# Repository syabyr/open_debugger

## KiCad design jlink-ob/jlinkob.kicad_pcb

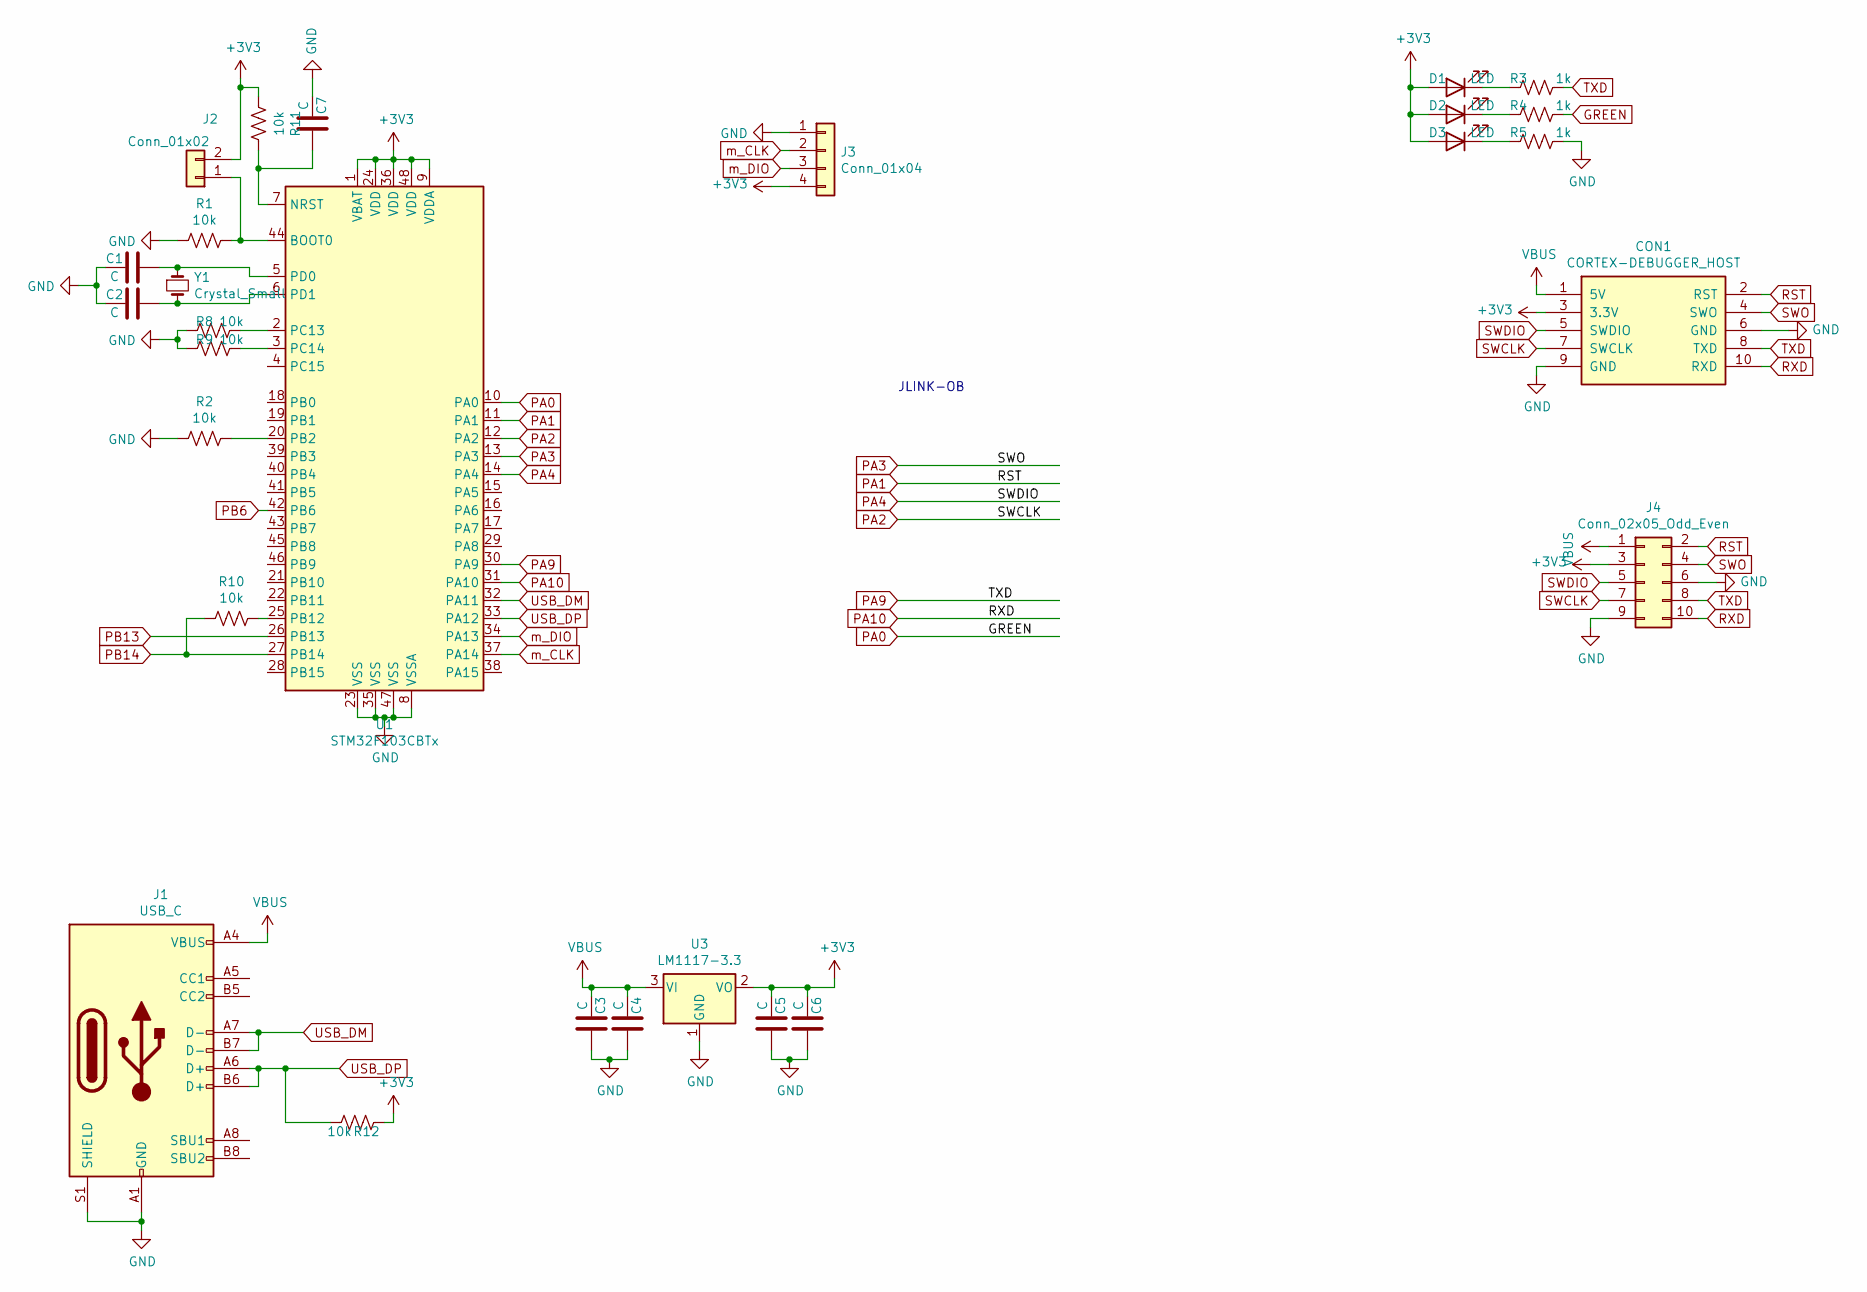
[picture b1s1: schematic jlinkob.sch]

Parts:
C1, C2, C3, C5, C7: C; C_0603_1608Metric
C4, C6: C; CP_EIA-7343-43_Kemet-X_Pad2.25x2.55mm_HandSolder
CON1: CORTEX-DEBUGGER_HOST; debugger_2x05_P1.27mm_Vertical
D1, D2, D3: LED; LED_0603_1608Metric
J1: USB_C
J2: Conn_01x02; PinHeader_1x02_P2.00mm_Vertical
J3: Conn_01x04; PinHeader_1x04_P2.00mm_Vertical
J4: Conn_02x05_Odd_Even; S_2.54_2_5P_JX
R1, R2, R8, R9, R10, R11, R12: 10k; R_0603_1608Metric
R3, R4, R5: 1k; R_0603_1608Metric
U1: STM32F103CBTx; LQFP-48_7x7mm_P0.5mm
U3: LM1117-3.3; SOT-223
Y1: Crystal_Small; Crystal_SMD_5032-2Pin_5.0x3.2mm

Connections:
+3V3: C5.2, C6.2, CON1.3 (3.3V), D1.2 (A), D2.2 (A), D3.2 (A), J2.2, J3.4, J4.3, R11.2, R12.2, U1.1 (VBAT), U1.9 (VDDA), U1.24 (VDD), U1.36 (VDD), U1.48 (VDD), U3.2 (VO)
GND: C1.2, C2.2, C3.1, C4.1, C5.1, C6.1, C7.2, CON1.6 (GND), CON1.9 (GND), J1.A1 (GND), J1.A12 (GND), J1.B1 (GND), J1.B12 (GND), J1.S1 (SHIELD), J3.1, J4.6, J4.9, R1.2, R2.2, R5.1, R8.2, R9.2, U1.8 (VSSA), U1.23 (VSS), U1.35 (VSS), U1.47 (VSS), U3.1 (GND)
GREEN: R4.1, U1.10 (PA0)
unnamed: C1.1, U1.5 (PD0), Y1.1
unnamed: C2.1, U1.6 (PD1), Y1.2
unnamed: C7.1, R11.1, U1.7 (NRST)
unnamed: D1.1 (K), R3.2
unnamed: D2.1 (K), R4.2
unnamed: D3.1 (K), R5.2
unnamed: J2.1, R1.1, U1.44 (BOOT0)
unnamed: R2.1, U1.20 (PB2)
unnamed: R8.1, U1.2 (PC13)
unnamed: R9.1, U1.3 (PC14)
unnamed: R10.1, U1.25 (PB12)
PA1: CON1.2 (RST), J4.2, U1.11 (PA1)
PA2: CON1.7 (SWCLK), J4.7, U1.12 (PA2)
PA3: CON1.4 (SWO), J4.4, U1.13 (PA3)
PA4: CON1.5 (SWDIO), J4.5, U1.14 (PA4)
PA9: CON1.8 (TXD), J4.8, R3.1, U1.30 (PA9)
PA10: CON1.10 (RXD), J4.10, U1.31 (PA10)
PB6: U1.42 (PB6)
PB13: U1.26 (PB13)
PB14: R10.2, U1.27 (PB14)
USB_DM: J1.A7 (D-), J1.B7 (D-), U1.32 (PA11)
USB_DP: J1.A6 (D+), J1.B6 (D+), R12.1, U1.33 (PA12)
VBUS: C3.2, C4.2, CON1.1 (5V), J1.A4 (VBUS), J1.A9 (VBUS), J1.B4 (VBUS), J1.B9 (VBUS), J4.1, U3.3 (VI)
m_CLK: J3.2, U1.37 (PA14)
m_DIO: J3.3, U1.34 (PA13)

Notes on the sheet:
JLINK-OB

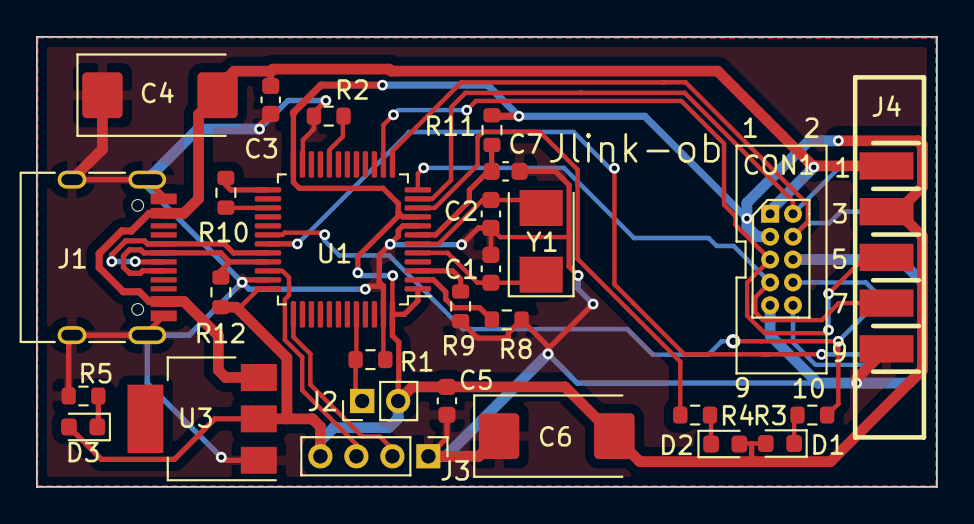
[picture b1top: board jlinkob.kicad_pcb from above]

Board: 2 copper layers, 50.0 x 25.0 mm, 28 parts (0 on the bottom side), 26 nets.

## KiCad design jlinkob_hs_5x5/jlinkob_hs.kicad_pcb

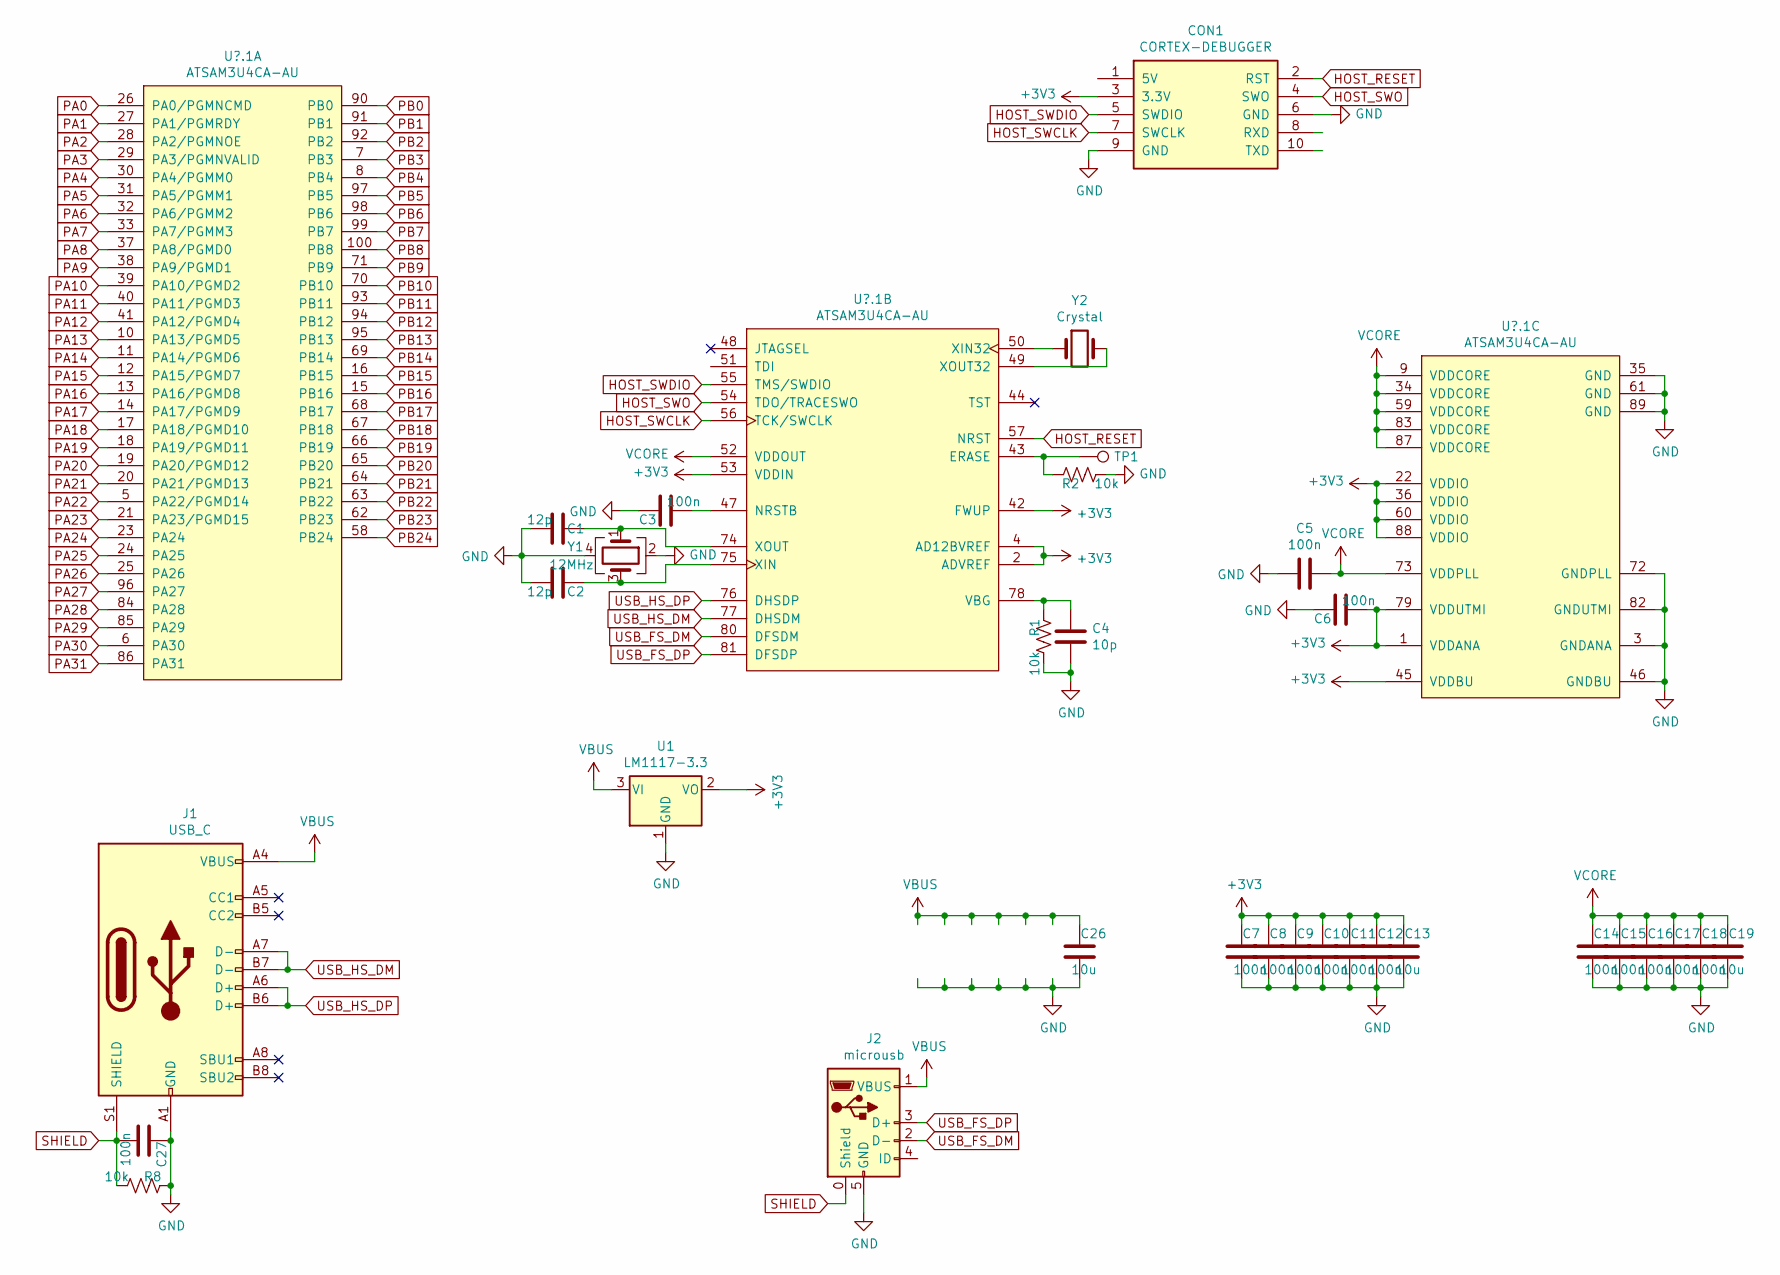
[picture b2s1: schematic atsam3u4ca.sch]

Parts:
C1, C2: 12p; C_0402_1005Metric_Pad0.74x0.62mm_HandSolder
C3, C5, C6, C7, C8, C9, C10, C11, C12, C14, C15, C16, C17, C18, C27: 100n; C_0402_1005Metric_Pad0.74x0.62mm_HandSolder
C4: 10p; C_0402_1005Metric_Pad0.74x0.62mm_HandSolder
C13, C26: 10u; C_1206_3216Metric_Pad1.33x1.80mm_HandSolder
C19: 10u; C_0402_1005Metric_Pad0.74x0.62mm_HandSolder
CON1: CORTEX-DEBUGGER; debugger_2x05_P1.27mm_Vertical
J1: USB_C
J2: microusb; USB_Micro-B_Wuerth_629105150521_CircularHoles
R1, R2, R8: 10k; R_0402_1005Metric_Pad0.72x0.64mm_HandSolder
TP1: TestPoint; TestPoint_0.5
U1: LM1117-3.3; SOT-223-3_TabPin2
U?.1: ATSAM3U4CA-AU; QFP50P1600X1600X160-100N
Y1: 12MHz; Crystal_SMD_3225-4Pin_3.2x2.5mm
Y2: Crystal; Crystal_SMD_MicroCrystal_CC7V-T1A-2Pin_3.2x1.5mm_HandSolder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

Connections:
+3V3: C6.2, C7.1, C8.1, C9.1, C10.1, C11.1, C12.1, C13.1, CON1.3 (3.3V), U1.2 (VO), U?.1.1 (VDDANA), U?.1.2 (ADVREF), U?.1.4 (AD12BVREF), U?.1.22 (VDDIO), U?.1.36 (VDDIO), U?.1.42 (FWUP), U?.1.45 (VDDBU), U?.1.53 (VDDIN), U?.1.60 (VDDIO), U?.1.79 (VDDUTMI), U?.1.88 (VDDIO); also elsewhere on the board
GND: C1.1, C2.1, C3.1, C4.2, C5.1, C6.1, C7.2, C8.2, C9.2, C10.2, C11.2, C12.2, C13.2, C14.2, C15.2, C16.2, C17.2, C18.2, C19.2, C26.2, C27.1, CON1.6 (GND), CON1.9 (GND), J1.A1 (GND), J1.A12 (GND), J1.B1 (GND), J1.B12 (GND), J2.5 (GND), R1.2, R2.2, R8.1, U1.1 (GND), U?.1.3 (GNDANA), U?.1.35 (GND), U?.1.46 (GNDBU), U?.1.61 (GND), U?.1.72 (GNDPLL), U?.1.82 (GNDUTMI), U?.1.89 (GND), Y1.2, Y1.4; also elsewhere on the board
HOST_RESET: CON1.2 (RST), U?.1.57 (NRST); also elsewhere on the board
HOST_SWCLK: CON1.7 (SWCLK), U?.1.56 (TCK/SWCLK)
HOST_SWDIO: CON1.5 (SWDIO), U?.1.55 (TMS/SWDIO)
HOST_SWO: CON1.4 (SWO), U?.1.54 (TDO/TRACESWO)
unnamed: C1.2, U?.1.74 (XOUT), Y1.1
unnamed: C2.2, U?.1.75 (XIN), Y1.3
unnamed: C3.2, U?.1.47 (NRSTB)
unnamed: C4.1, R1.1, U?.1.78 (VBG)
unnamed: R2.1, TP1.1, U?.1.43 (ERASE)
unnamed: U?.1.49 (XOUT32), Y2.2
unnamed: U?.1.50 (XIN32), Y2.1
PA0: U?.1.26 (PA0/PGMNCMD); also elsewhere on the board
PA1: U?.1.27 (PA1/PGMRDY); also elsewhere on the board
PA2: U?.1.28 (PA2/PGMNOE); also elsewhere on the board
PA3: U?.1.29 (PA3/PGMNVALID); also elsewhere on the board
PA4: U?.1.30 (PA4/PGMM0); also elsewhere on the board
PA5: U?.1.31 (PA5/PGMM1); also elsewhere on the board
PA6: U?.1.32 (PA6/PGMM2); also elsewhere on the board
PA7: U?.1.33 (PA7/PGMM3); also elsewhere on the board
PA8: U?.1.37 (PA8/PGMD0); also elsewhere on the board
PA9: U?.1.38 (PA9/PGMD1); also elsewhere on the board
PA10: U?.1.39 (PA10/PGMD2); also elsewhere on the board
PA11: U?.1.40 (PA11/PGMD3); also elsewhere on the board
PA12: U?.1.41 (PA12/PGMD4); also elsewhere on the board
PA13: U?.1.10 (PA13/PGMD5); also elsewhere on the board
PA14: U?.1.11 (PA14/PGMD6); also elsewhere on the board
PA15: U?.1.12 (PA15/PGMD7); also elsewhere on the board
PA16: U?.1.13 (PA16/PGMD8); also elsewhere on the board
PA17: U?.1.14 (PA17/PGMD9); also elsewhere on the board
PA18: U?.1.17 (PA18/PGMD10); also elsewhere on the board
PA19: U?.1.18 (PA19/PGMD11); also elsewhere on the board
PA20: U?.1.19 (PA20/PGMD12); also elsewhere on the board
PA21: U?.1.20 (PA21/PGMD13); also elsewhere on the board
PA22: U?.1.5 (PA22/PGMD14); also elsewhere on the board
PA23: U?.1.21 (PA23/PGMD15); also elsewhere on the board
PA24: U?.1.23 (PA24); also elsewhere on the board
PA25: U?.1.24 (PA25); also elsewhere on the board
PA26: U?.1.25 (PA26); also elsewhere on the board
PA27: U?.1.96 (PA27); also elsewhere on the board
PA28: U?.1.84 (PA28); also elsewhere on the board
PA29: U?.1.85 (PA29); also elsewhere on the board
PA30: U?.1.6 (PA30); also elsewhere on the board
PA31: U?.1.86 (PA31); also elsewhere on the board
PB0: U?.1.90 (PB0); also elsewhere on the board
PB1: U?.1.91 (PB1); also elsewhere on the board
PB2: U?.1.92 (PB2); also elsewhere on the board
PB3: U?.1.7 (PB3); also elsewhere on the board
PB4: U?.1.8 (PB4); also elsewhere on the board
PB5: U?.1.97 (PB5); also elsewhere on the board
PB6: U?.1.98 (PB6); also elsewhere on the board
PB7: U?.1.99 (PB7); also elsewhere on the board
PB8: U?.1.100 (PB8); also elsewhere on the board
PB9: U?.1.71 (PB9); also elsewhere on the board
PB10: U?.1.70 (PB10); also elsewhere on the board
PB11: U?.1.93 (PB11); also elsewhere on the board
PB12: U?.1.94 (PB12); also elsewhere on the board
PB13: U?.1.95 (PB13); also elsewhere on the board
PB14: U?.1.69 (PB14); also elsewhere on the board
PB15: U?.1.16 (PB15); also elsewhere on the board
PB16: U?.1.15 (PB16); also elsewhere on the board
PB17: U?.1.68 (PB17); also elsewhere on the board
PB18: U?.1.67 (PB18); also elsewhere on the board
PB19: U?.1.66 (PB19); also elsewhere on the board
PB20: U?.1.65 (PB20); also elsewhere on the board
PB21: U?.1.64 (PB21); also elsewhere on the board
PB22: U?.1.63 (PB22); also elsewhere on the board
PB23: U?.1.62 (PB23); also elsewhere on the board
PB24: U?.1.58 (PB24); also elsewhere on the board
SHIELD: C27.2, J1.S1 (SHIELD), J2.0 (Shield), R8.2
USB_FS_DM: J2.2 (D-), U?.1.80 (DFSDM)
USB_FS_DP: J2.3 (D+), U?.1.81 (DFSDP)
USB_HS_DM: J1.A7 (D-), J1.B7 (D-), U?.1.77 (DHSDM)
USB_HS_DP: J1.A6 (D+), J1.B6 (D+), U?.1.76 (DHSDP)
VBUS: C26.1, J1.A4 (VBUS), J1.A9 (VBUS), J1.B4 (VBUS), J1.B9 (VBUS), J2.1 (VBUS), U1.3 (VI)
VCC: C5.2, C14.1, C15.1, C16.1, C17.1, C18.1, C19.1, U?.1.9 (VDDCORE), U?.1.34 (VDDCORE), U?.1.52 (VDDOUT), U?.1.59 (VDDCORE), U?.1.73 (VDDPLL), U?.1.83 (VDDCORE), U?.1.87 (VDDCORE); also elsewhere on the board

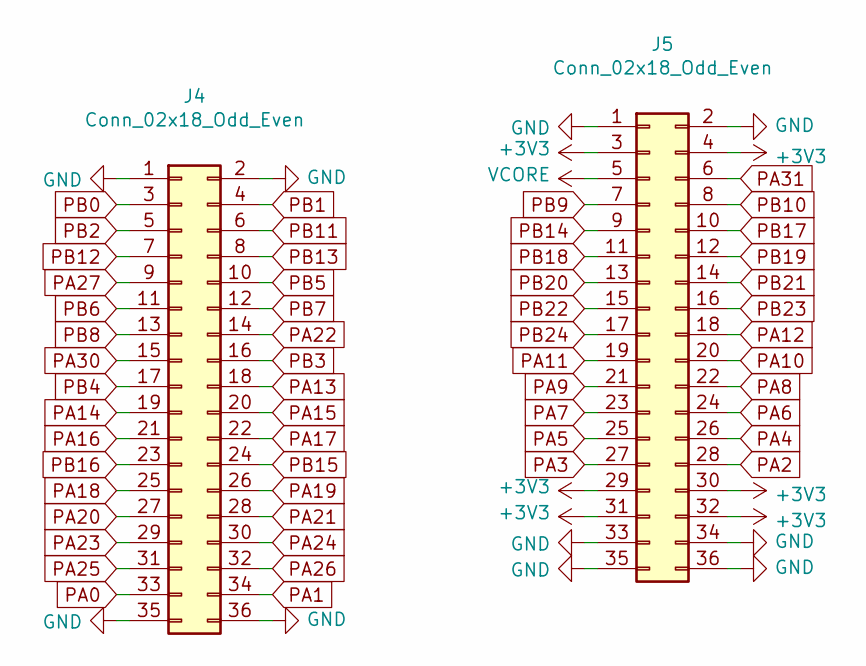
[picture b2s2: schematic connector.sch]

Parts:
J4, J5: Conn_02x18_Odd_Even; PinHeader_2x18_P2.54mm_Vertical

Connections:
+3V3: J5.3, J5.4, J5.29, J5.30, J5.31, J5.32; also elsewhere on the board
GND: J4.1, J4.2, J4.35, J4.36, J5.1, J5.2, J5.33, J5.34, J5.35, J5.36; also elsewhere on the board
PA0: J4.33; also elsewhere on the board
PA1: J4.34; also elsewhere on the board
PA2: J5.28; also elsewhere on the board
PA3: J5.27; also elsewhere on the board
PA4: J5.26; also elsewhere on the board
PA5: J5.25; also elsewhere on the board
PA6: J5.24; also elsewhere on the board
PA7: J5.23; also elsewhere on the board
PA8: J5.22; also elsewhere on the board
PA9: J5.21; also elsewhere on the board
PA10: J5.20; also elsewhere on the board
PA11: J5.19; also elsewhere on the board
PA12: J5.18; also elsewhere on the board
PA13: J4.18; also elsewhere on the board
PA14: J4.19; also elsewhere on the board
PA15: J4.20; also elsewhere on the board
PA16: J4.21; also elsewhere on the board
PA17: J4.22; also elsewhere on the board
PA18: J4.25; also elsewhere on the board
PA19: J4.26; also elsewhere on the board
PA20: J4.27; also elsewhere on the board
PA21: J4.28; also elsewhere on the board
PA22: J4.14; also elsewhere on the board
PA23: J4.29; also elsewhere on the board
PA24: J4.30; also elsewhere on the board
PA25: J4.31; also elsewhere on the board
PA26: J4.32; also elsewhere on the board
PA27: J4.9; also elsewhere on the board
PA30: J4.15; also elsewhere on the board
PA31: J5.6; also elsewhere on the board
PB0: J4.3; also elsewhere on the board
PB1: J4.4; also elsewhere on the board
PB2: J4.5; also elsewhere on the board
PB3: J4.16; also elsewhere on the board
PB4: J4.17; also elsewhere on the board
PB5: J4.10; also elsewhere on the board
PB6: J4.11; also elsewhere on the board
PB7: J4.12; also elsewhere on the board
PB8: J4.13; also elsewhere on the board
PB9: J5.7; also elsewhere on the board
PB10: J5.8; also elsewhere on the board
PB11: J4.6; also elsewhere on the board
PB12: J4.7; also elsewhere on the board
PB13: J4.8; also elsewhere on the board
PB14: J5.9; also elsewhere on the board
PB15: J4.24; also elsewhere on the board
PB16: J4.23; also elsewhere on the board
PB17: J5.10; also elsewhere on the board
PB18: J5.11; also elsewhere on the board
PB19: J5.12; also elsewhere on the board
PB20: J5.13; also elsewhere on the board
PB21: J5.14; also elsewhere on the board
PB22: J5.15; also elsewhere on the board
PB23: J5.16; also elsewhere on the board
PB24: J5.17; also elsewhere on the board
VCC: J5.5; also elsewhere on the board

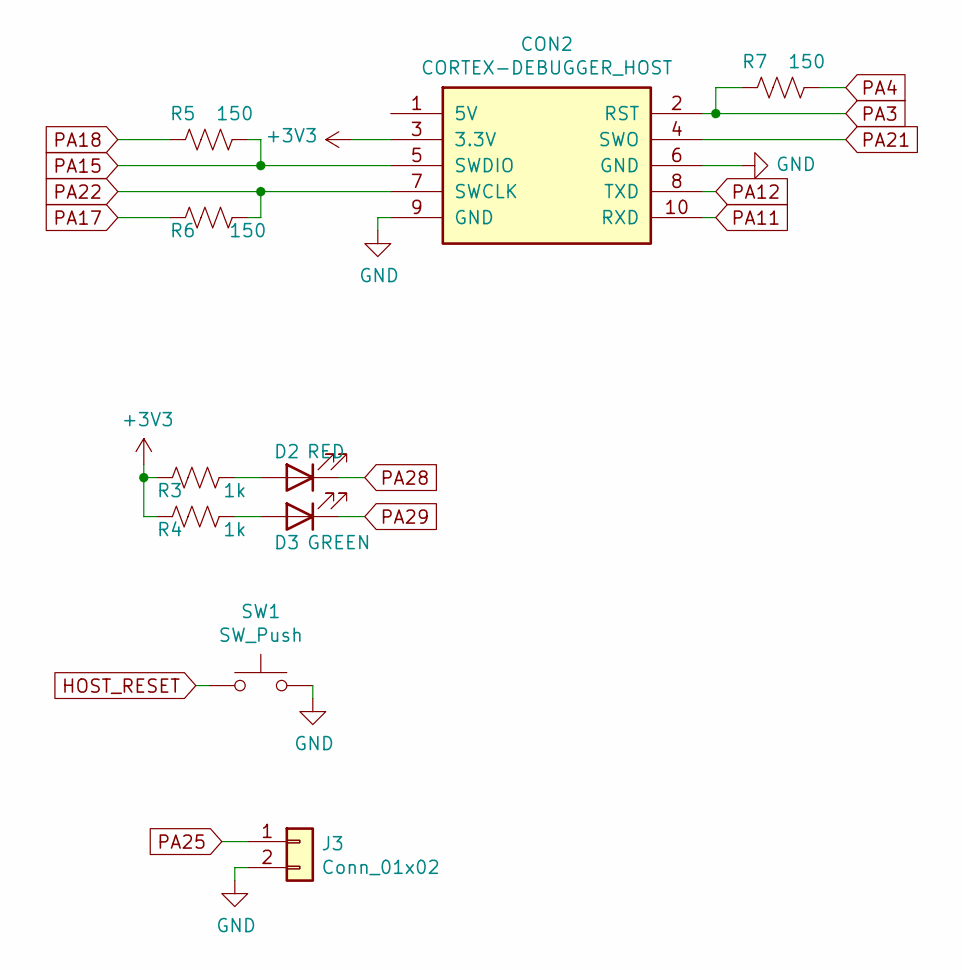
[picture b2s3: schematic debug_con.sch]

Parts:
CON2: CORTEX-DEBUGGER_HOST; debugger_2x05_P1.27mm_Vertical
D2: RED; LED_0603_1608Metric_Castellated
D3: GREEN; LED_0603_1608Metric_Castellated
J3: Conn_01x02; PinHeader_1x02_P2.00mm_Vertical
R3, R4: 1k; R_0402_1005Metric_Pad0.72x0.64mm_HandSolder
R5, R6, R7: 150; R_0402_1005Metric_Pad0.72x0.64mm_HandSolder
SW1: SW_Push; turtlekey

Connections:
+3V3: CON2.3 (3.3V), R3.2, R4.2; also elsewhere on the board
GND: CON2.6 (GND), CON2.9 (GND), J3.2, SW1.2; also elsewhere on the board
HOST_RESET: SW1.1; also elsewhere on the board
unnamed: D2.2 (A), R3.1
unnamed: D3.2 (A), R4.1
PA3: CON2.2 (RST), R7.2; also elsewhere on the board
PA4: R7.1; also elsewhere on the board
PA11: CON2.10 (RXD); also elsewhere on the board
PA12: CON2.8 (TXD); also elsewhere on the board
PA15: CON2.5 (SWDIO), R5.1; also elsewhere on the board
PA17: R6.2; also elsewhere on the board
PA18: R5.2; also elsewhere on the board
PA21: CON2.4 (SWO); also elsewhere on the board
PA22: CON2.7 (SWCLK), R6.1; also elsewhere on the board
PA25: J3.1; also elsewhere on the board
PA28: D2.1 (K); also elsewhere on the board
PA29: D3.1 (K); also elsewhere on the board

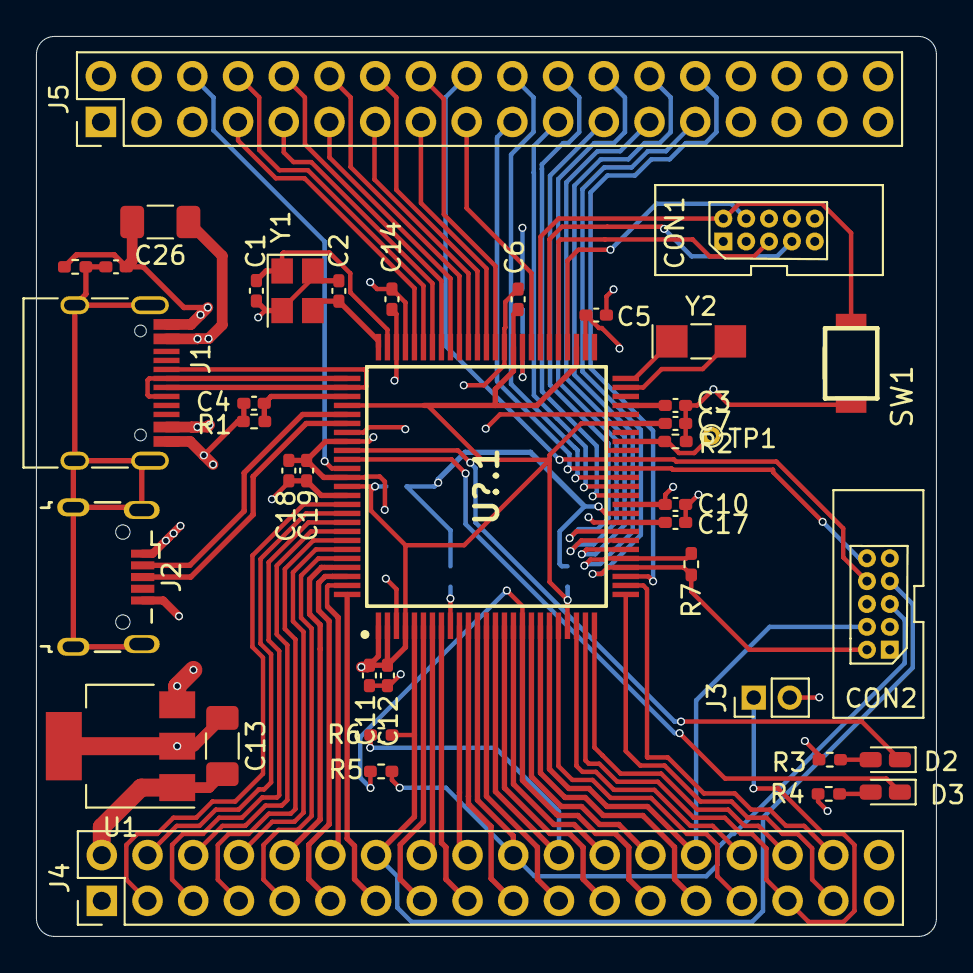
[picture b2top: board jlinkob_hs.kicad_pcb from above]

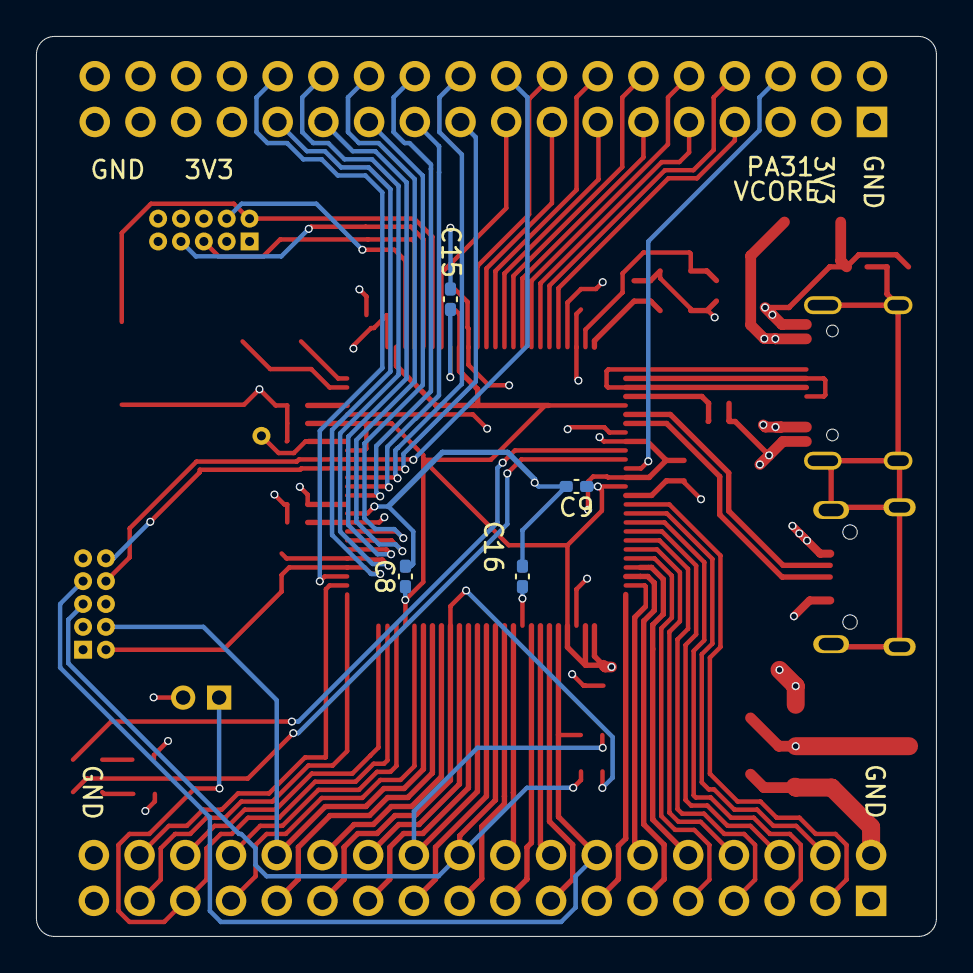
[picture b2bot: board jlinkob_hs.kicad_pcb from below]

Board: 4 copper layers, 50.0 x 50.0 mm, 44 parts (4 on the bottom side), 79 nets.

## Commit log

2021-02-06 init
2021-02-06 seperate
2021-02-14 20210214
2021-02-14 gerber
2021-02-14 silk
2021-02-14 3d module
2021-02-21 rev2
2021-03-03 firmware
2021-03-03 jlinkob
2021-03-06 3d case
2021-03-11 stlinkv21
2021-03-12 jlink-ob
2021-08-18 jlinkob_hs
2021-08-18 20210818
